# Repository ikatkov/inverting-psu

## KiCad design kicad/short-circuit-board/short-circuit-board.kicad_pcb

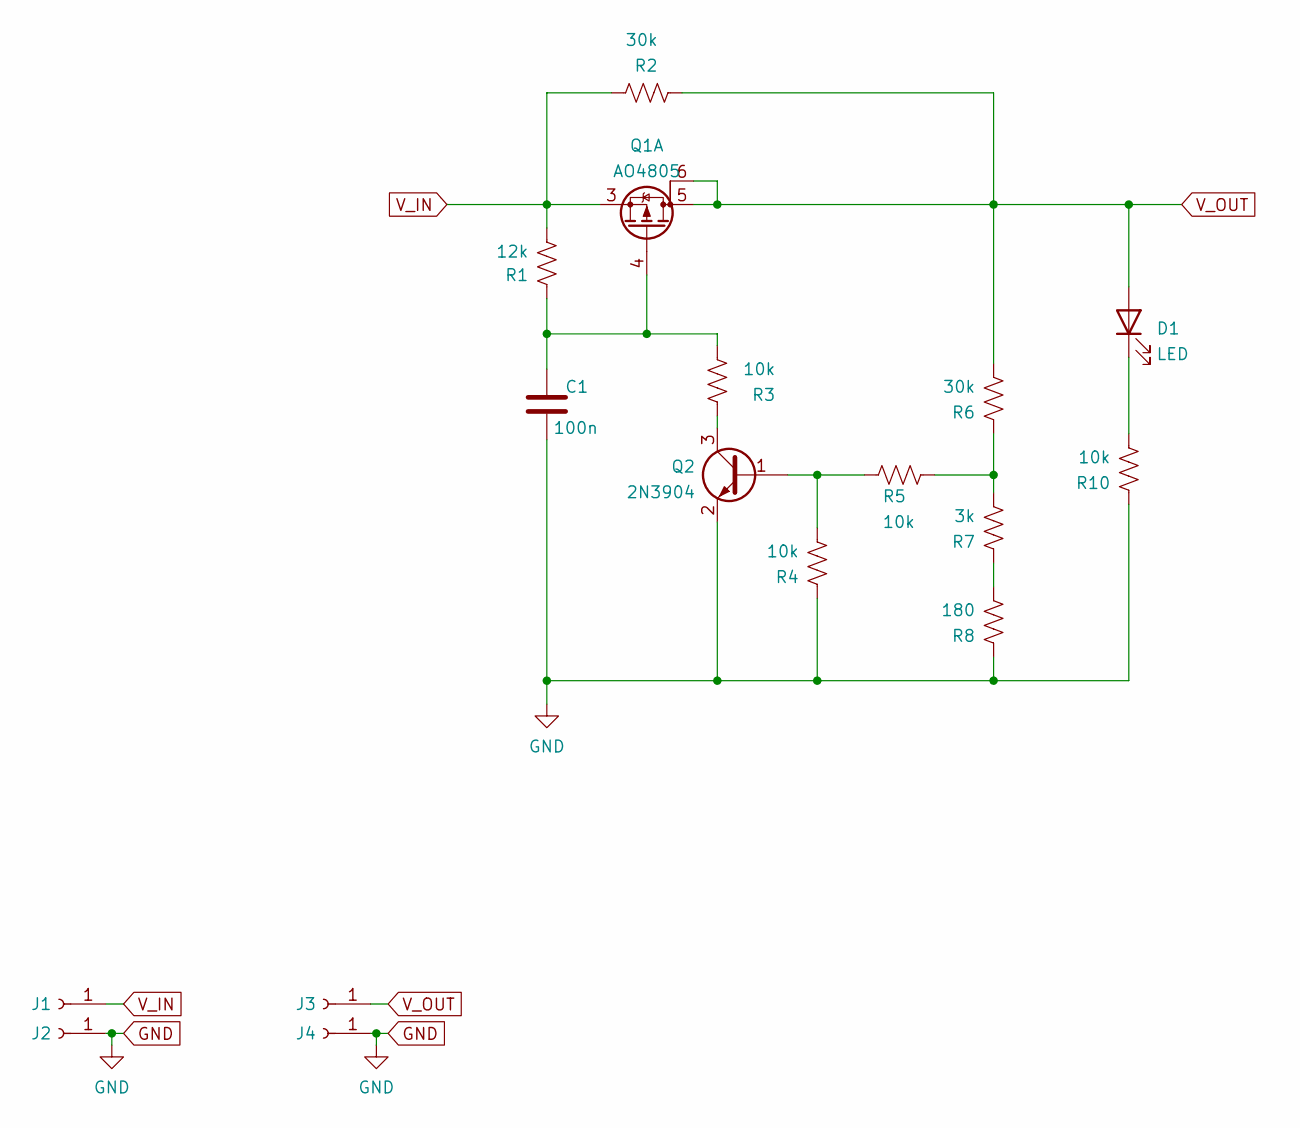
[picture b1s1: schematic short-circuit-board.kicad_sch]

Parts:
C1: 100n; C_1206_3216Metric
D1: LED; LED_0805_2012Metric
J1: Vin; SolderWire-0.5sqmm_1x01_D0.9mm_OD2.3mm
J2, J4: GND; SolderWire-0.5sqmm_1x01_D0.9mm_OD2.3mm
J3: Vout; SolderWire-0.5sqmm_1x01_D0.9mm_OD2.3mm
Q1: AO4805; SOIC-8_3.9x4.9mm_P1.27mm
Q2: 2N3904; SOT-23
R1: 12k; R_0805_2012Metric
R2, R6: 30k; R_0805_2012Metric
R3, R4, R5, R10: 10k; R_0805_2012Metric
R7: 3k; R_0805_2012Metric
R8: 180; R_0805_2012Metric

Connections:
GND: C1.2, J2.1, J4.1, Q2.2 (E), R4.1, R8.1, R10.1
unnamed: C1.1, Q1.4 (G1), R1.1, R3.2
unnamed: D1.1 (K), R10.2
unnamed: Q2.1 (B), R4.2, R5.2
unnamed: Q2.3 (C), R3.1
unnamed: R5.1, R6.1, R7.2
unnamed: R7.1, R8.2
V_IN: J1.1, Q1.3 (S1), R1.2, R2.1
V_OUT: D1.2 (A), J3.1, Q1.5 (D1), Q1.6 (D1), R2.2, R6.2

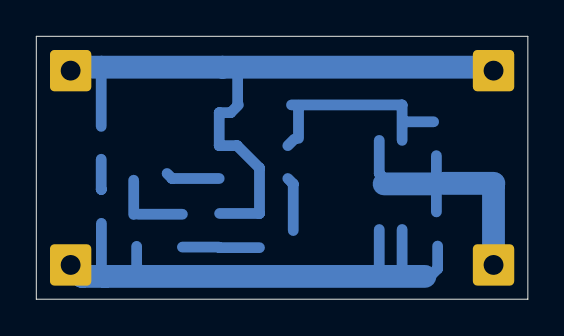
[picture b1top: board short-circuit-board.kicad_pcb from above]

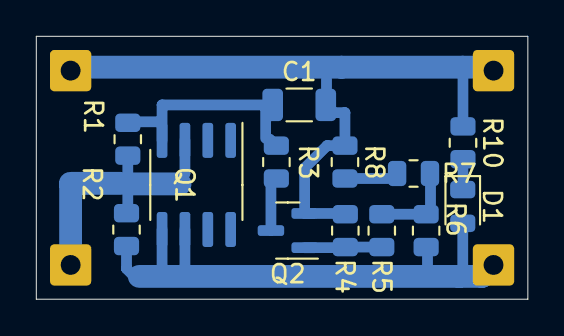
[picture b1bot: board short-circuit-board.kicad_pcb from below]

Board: 4 copper layers, 27.3 x 14.6 mm, 17 parts (17 on the bottom side), 9 nets.

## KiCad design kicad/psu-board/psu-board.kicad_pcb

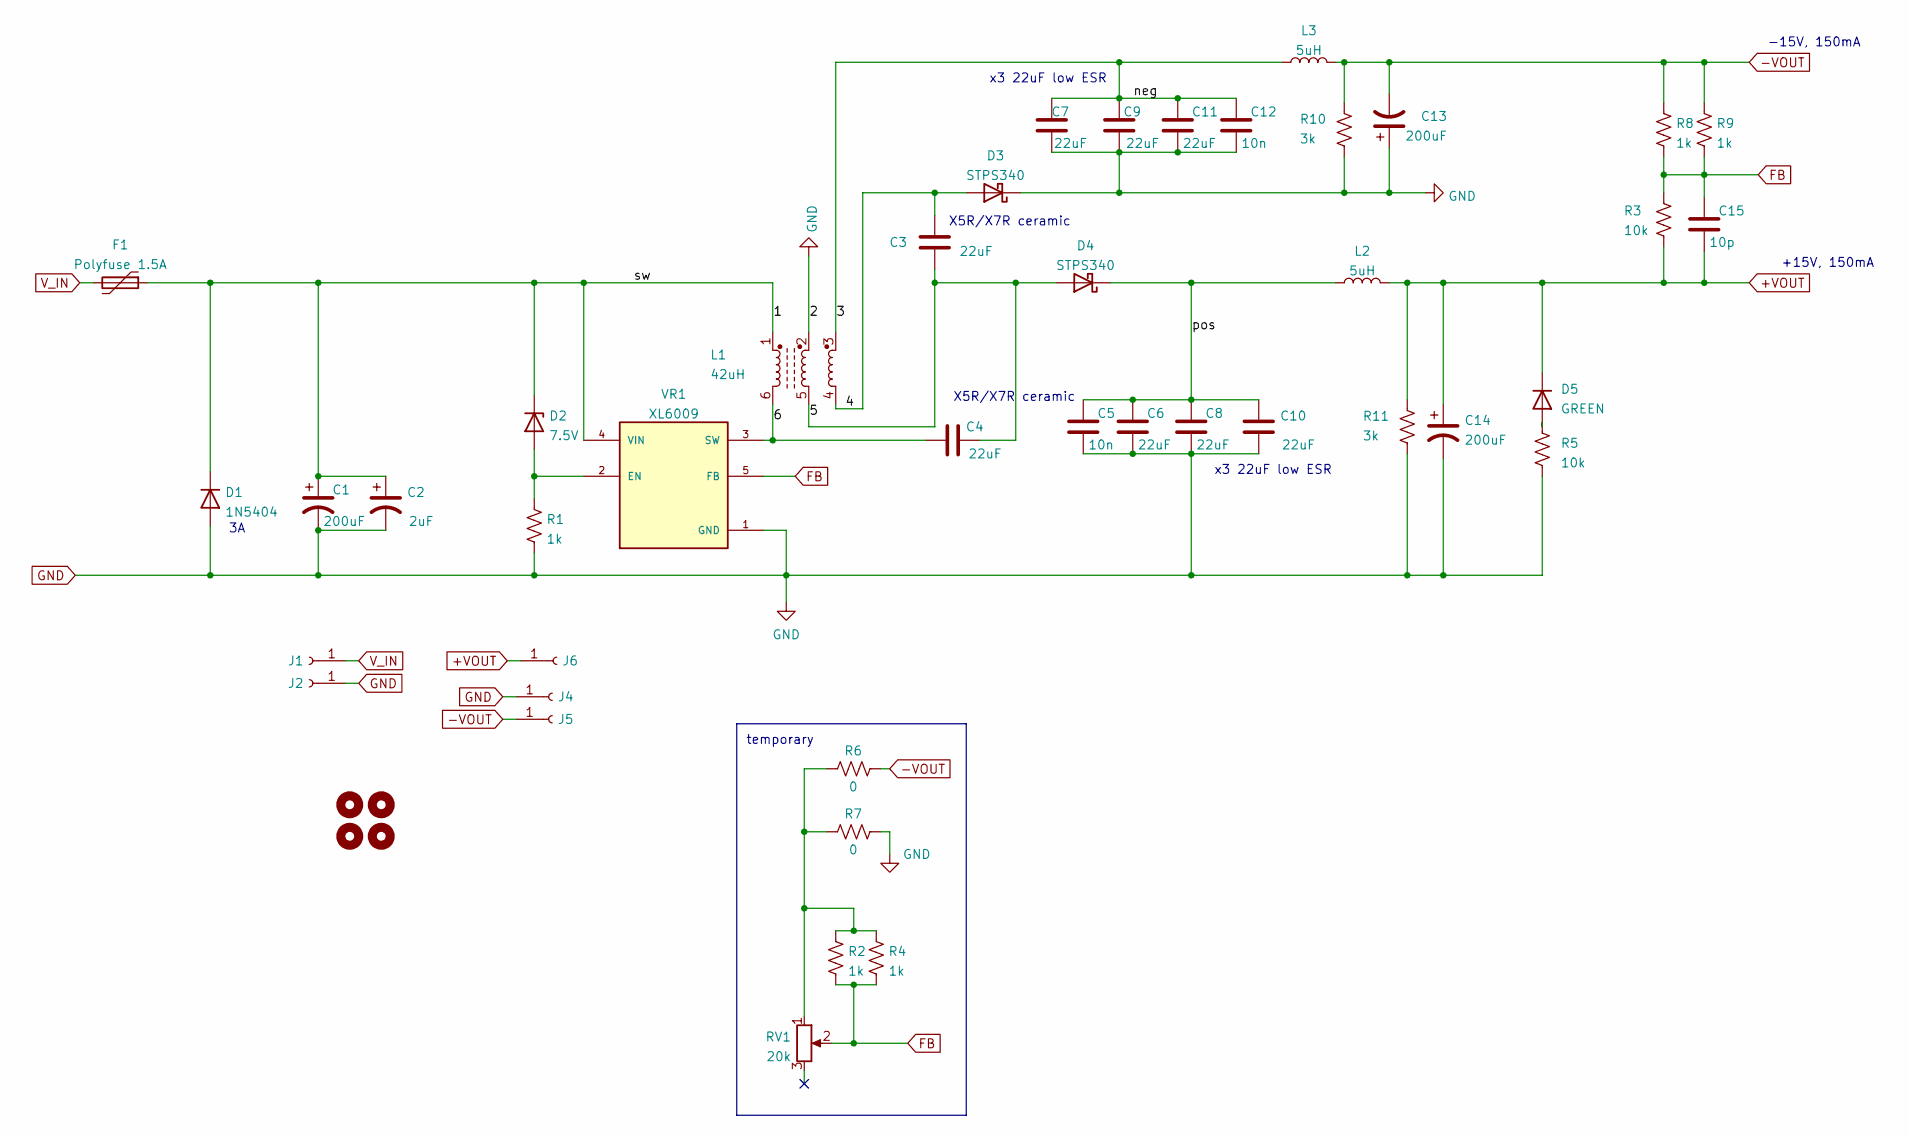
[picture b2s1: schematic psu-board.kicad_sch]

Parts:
C1, C13, C14: 200uF; CP_Radial_D10.0mm_P5.00mm
C2: 2uF; C_1206_3216Metric
C3, C4, C6, C7, C8, C9, C10, C11: 22uF; C_1206_3216Metric
C5, C12: 10n; C_1206_3216Metric
C15: 10p; C_1206_3216Metric
D1: 1N5404; D_DO-41_SOD81_P3.81mm_Vertical_AnodeUp
D2: 7.5V; D_MiniMELF
D3, D4: STPS340; D_SMB
D5: GREEN; LED_D5.0mm
F1: Polyfuse 1.5A; R_1812_4532Metric
H1, H2, H3, H4: MountingHole; MountingHole_3mm
J1: Vin; SolderWire-0.5sqmm_1x01_D0.9mm_OD2.3mm
J2, J4: GND; SolderWire-0.5sqmm_1x01_D0.9mm_OD2.3mm
J5: Vout-; SolderWire-0.5sqmm_1x01_D0.9mm_OD2.3mm
J6: Vout+; SolderWire-0.5sqmm_1x01_D0.9mm_OD2.3mm
L1: 42uH; inductor-3filar
L2, L3: 5uH; CP_Radial_D6.3mm_P2.50mm
R1, R2, R4, R8, R9: 1k; R_0805_2012Metric
R3, R5: 10k; R_0805_2012Metric
R6, R7: 0; R_0805_2012Metric
R10, R11: 3k; R_0805_2012Metric
RV1: 20k; Potentiometer_Bourns_3296W_Vertical
VR1: XL6009; XL6009-DPAK; PARTREV 1.1

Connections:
+VOUT: C14.1, C15.2, D5.1 (K), J6.1, L2.2, R3.2, R11.1
-VOUT: C13.2, J5.1, L3.2, R6.2, R8.1, R9.1, R10.1
/1: C1.1, C2.1, D1.1 (K), D2.1 (K), F1.1, L1.1, VR1.4 (VIN)
/3: C7.2, C9.2, C11.1, C12.1, L1.3, L3.1
/4: C3.2, D3.2 (A), L1.4
/5: C3.1, C4.2, D4.2 (A), L1.5
/6: C4.1, L1.6, VR1.3 (SW)
/pos: C5.1, C6.1, C8.1, C10.1, D4.1 (K), L2.1
FB: C15.1, R2.2, R3.1, R4.2, R8.2, R9.2, RV1.2, VR1.5 (FB)
GND: C1.2, C2.2, C5.2, C6.2, C7.1, C8.2, C9.1, C10.2, C11.2, C12.2, C13.1, C14.2, D1.2 (A), D3.1 (K), J2.1, J4.1, L1.2, R1.2, R5.2, R7.2, R10.2, R11.2, VR1.1 (GND)
unnamed: D2.2 (A), R1.1, VR1.2 (EN)
unnamed: D5.2 (A), R5.1
unnamed: R2.1, R4.1, R6.1, R7.1, RV1.1
V_IN: F1.2, J1.1

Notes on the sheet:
x3 22uF low ESR
-15V, 150mA
X5R/X7R ceramic
temporary
+15V, 150mA

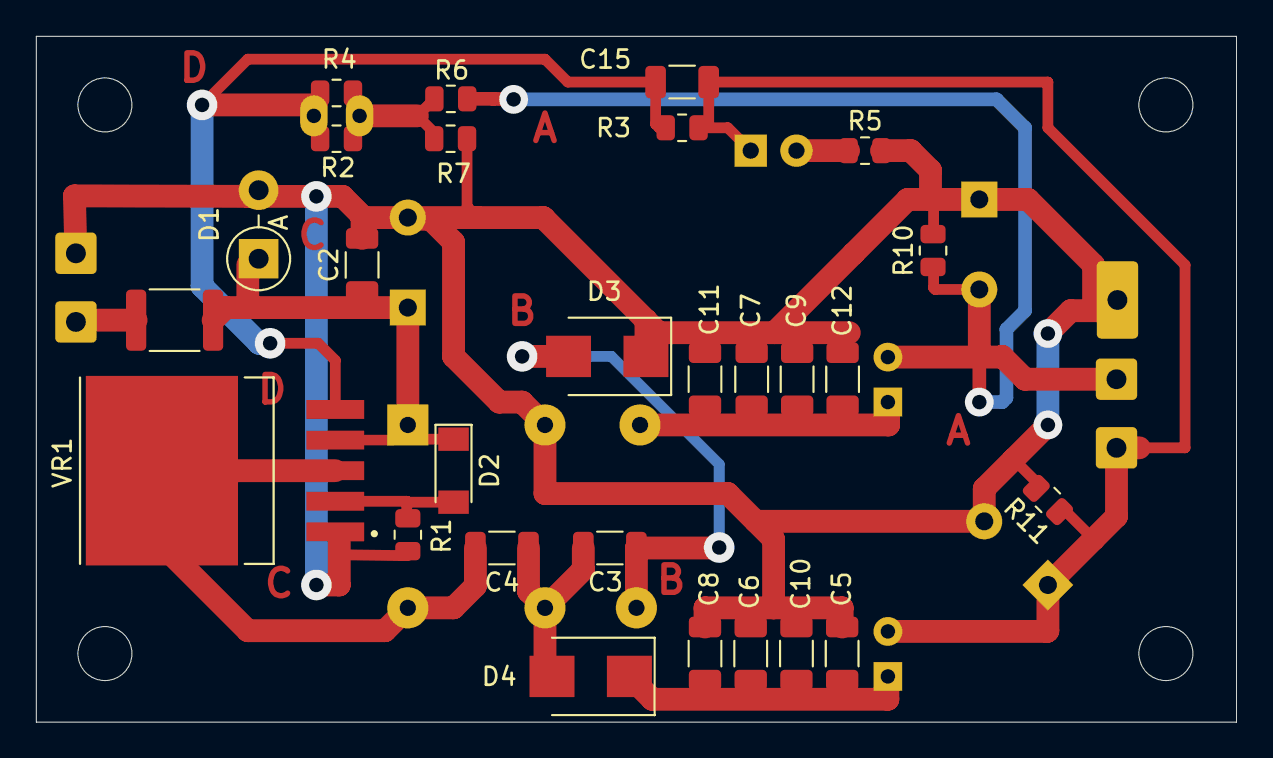
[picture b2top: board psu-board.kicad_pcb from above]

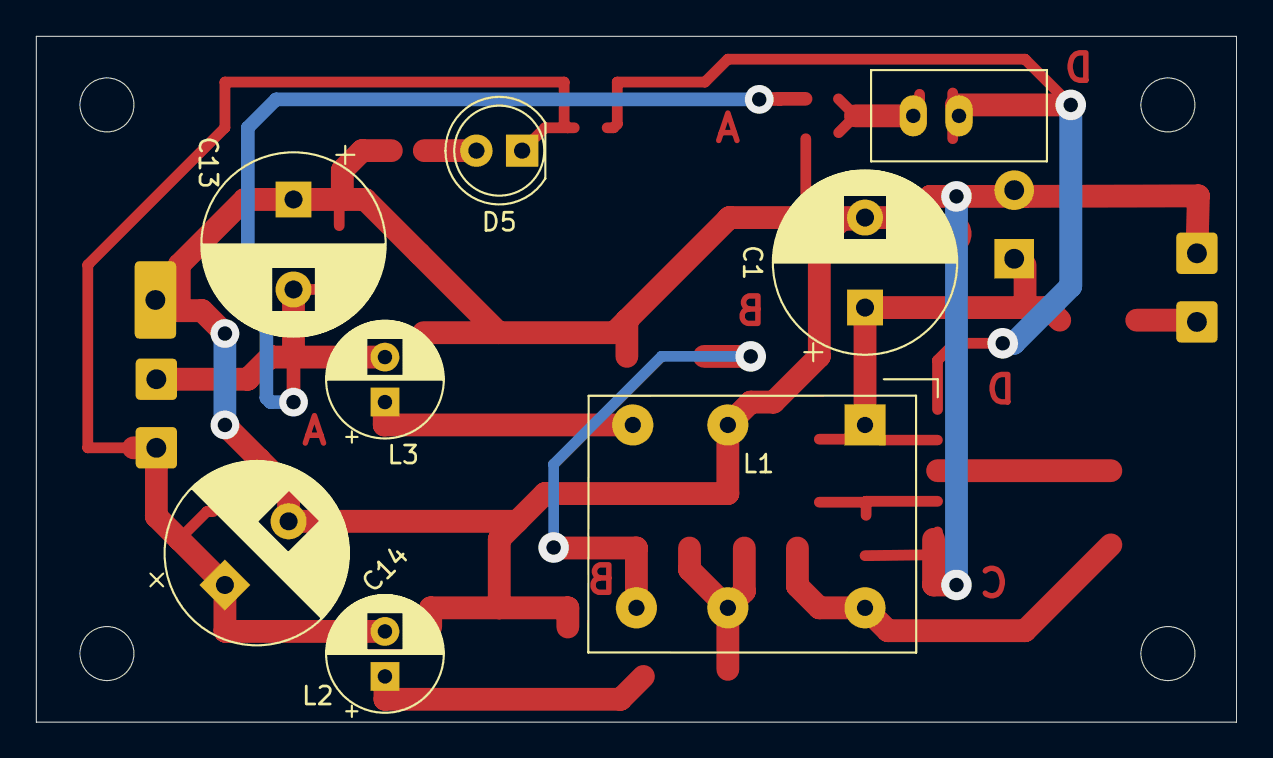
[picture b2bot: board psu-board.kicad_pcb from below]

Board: 4 copper layers, 66.7 x 38.1 mm, 44 parts (8 on the bottom side), 14 nets.

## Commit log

2023-04-22 more data
2023-04-22 add license
